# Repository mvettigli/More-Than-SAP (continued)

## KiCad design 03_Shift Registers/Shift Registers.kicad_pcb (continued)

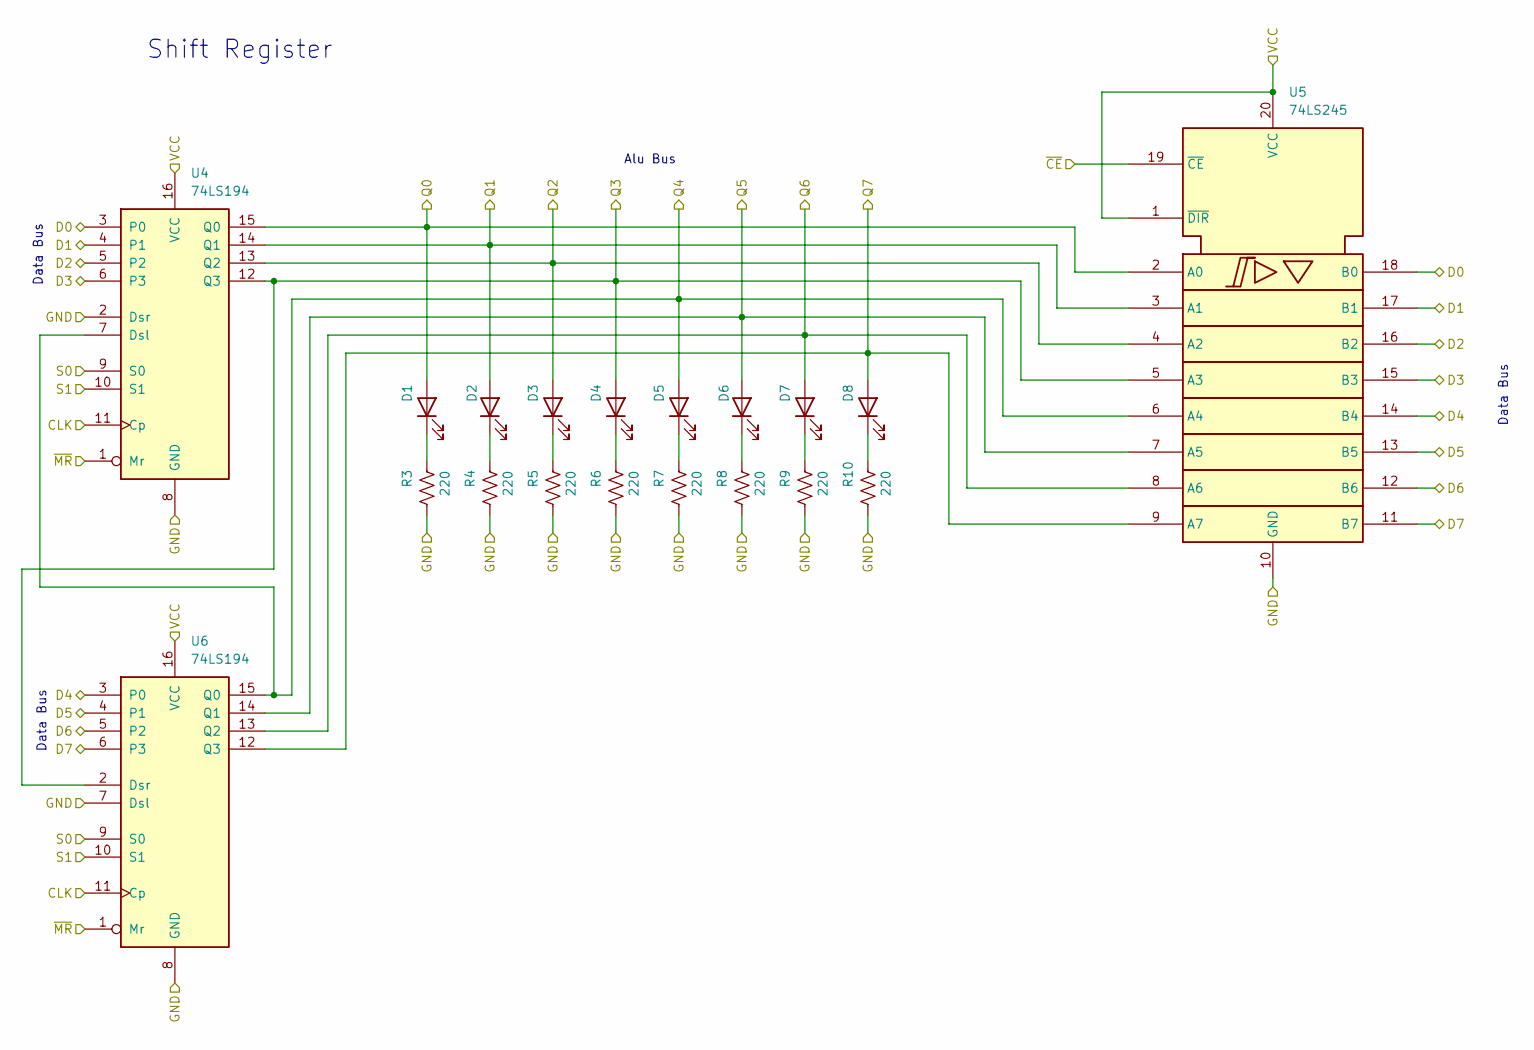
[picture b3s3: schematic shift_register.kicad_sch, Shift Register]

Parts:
D1, D2, D3, D4, D5, D6, D7, D8: RED; LED_D3.0mm
R3, R4, R5, R6, R7, R8, R9, R10: 220; R_Axial_DIN0207_L6.3mm_D2.5mm_P10.16mm_Horizontal
U4, U6: 74LS194; DIP-16_W7.62mm
U5: 74LS245; DIP-20_W7.62mm

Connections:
/Alu selector L-X/Q0: D1.2 (A), U4.15 (Q0), U5.2 (A0); also elsewhere on the board
/Alu selector L-X/Q1: D2.2 (A), U4.14 (Q1), U5.3 (A1); also elsewhere on the board
/Alu selector L-X/Q2: D3.2 (A), U4.13 (Q2), U5.4 (A2); also elsewhere on the board
/Alu selector L-X/Q3: D4.2 (A), U4.12 (Q3), U5.5 (A3), U6.2 (Dsr); also elsewhere on the board
/Alu selector L-X/Q4: D5.2 (A), U4.7 (Dsl), U5.6 (A4), U6.15 (Q0); also elsewhere on the board
/Alu selector L-X/Q5: D6.2 (A), U5.7 (A5), U6.14 (Q1); also elsewhere on the board
/Alu selector L-X/Q6: D7.2 (A), U5.8 (A6), U6.13 (Q2); also elsewhere on the board
/Alu selector L-X/Q7: D8.2 (A), U5.9 (A7), U6.12 (Q3); also elsewhere on the board
/Shift register L/S0: U4.9 (S0), U6.9 (S0); also elsewhere on the board
/Shift register L/S1: U4.10 (S1), U6.10 (S1); also elsewhere on the board
/Shift register L/~MR: U4.1 (Mr), U6.1 (Mr)
CLK: U4.11 (Cp), U6.11 (Cp); also elsewhere on the board
D0: U4.3 (P0), U5.18 (B0); also elsewhere on the board
D1: U4.4 (P1), U5.17 (B1); also elsewhere on the board
D2: U4.5 (P2), U5.16 (B2); also elsewhere on the board
D3: U4.6 (P3), U5.15 (B3); also elsewhere on the board
D4: U5.14 (B4), U6.3 (P0); also elsewhere on the board
D5: U5.13 (B5), U6.4 (P1); also elsewhere on the board
D6: U5.12 (B6), U6.5 (P2); also elsewhere on the board
D7: U5.11 (B7), U6.6 (P3); also elsewhere on the board
GND: R3.2, R4.2, R5.2, R6.2, R7.2, R8.2, R9.2, R10.2, U4.2 (Dsr), U4.8 (GND), U5.10 (GND), U6.7 (Dsl), U6.8 (GND); also elsewhere on the board
unnamed: D1.1 (K), R3.1
unnamed: D2.1 (K), R4.1
unnamed: D3.1 (K), R5.1
unnamed: D4.1 (K), R6.1
unnamed: D5.1 (K), R7.1
unnamed: D6.1 (K), R8.1
unnamed: D7.1 (K), R9.1
unnamed: D8.1 (K), R10.1
VCC: U4.16 (VCC), U5.1 (~DIR), U5.20 (VCC), U6.16 (VCC); also elsewhere on the board
~LRO: U5.19 (~CE); also elsewhere on the board

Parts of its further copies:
D9, D10, D11, D12, D13, D14, D15, D16: RED; LED_D3.0mm
R11, R12, R13, R14, R15, R16, R17, R18: 220; R_Axial_DIN0207_L6.3mm_D2.5mm_P10.16mm_Horizontal
U7, U9: 74LS194; DIP-16_W7.62mm
U8: 74LS245; DIP-20_W7.62mm

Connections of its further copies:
/Alu selector R-X/Q0: D9.2 (A), U7.15 (Q0), U8.2 (A0); also elsewhere on the board
/Alu selector R-X/Q1: D10.2 (A), U7.14 (Q1), U8.3 (A1); also elsewhere on the board
/Alu selector R-X/Q2: D11.2 (A), U7.13 (Q2), U8.4 (A2); also elsewhere on the board
/Alu selector R-X/Q3: D12.2 (A), U7.12 (Q3), U8.5 (A3), U9.2 (Dsr); also elsewhere on the board
/Alu selector R-X/Q4: D13.2 (A), U7.7 (Dsl), U8.6 (A4), U9.15 (Q0); also elsewhere on the board
/Alu selector R-X/Q5: D14.2 (A), U8.7 (A5), U9.14 (Q1); also elsewhere on the board
/Alu selector R-X/Q6: D15.2 (A), U8.8 (A6), U9.13 (Q2); also elsewhere on the board
/Alu selector R-X/Q7: D16.2 (A), U8.9 (A7), U9.12 (Q3); also elsewhere on the board
/Shift register R/S0: U7.9 (S0), U9.9 (S0); also elsewhere on the board
/Shift register R/S1: U7.10 (S1), U9.10 (S1); also elsewhere on the board
/Shift register R/~MR: U7.1 (Mr), U9.1 (Mr)
CLK: U7.11 (Cp), U9.11 (Cp); also elsewhere on the board
D0: U7.3 (P0), U8.18 (B0); also elsewhere on the board
D1: U7.4 (P1), U8.17 (B1); also elsewhere on the board
D2: U7.5 (P2), U8.16 (B2); also elsewhere on the board
D3: U7.6 (P3), U8.15 (B3); also elsewhere on the board
D4: U8.14 (B4), U9.3 (P0); also elsewhere on the board
D5: U8.13 (B5), U9.4 (P1); also elsewhere on the board
D6: U8.12 (B6), U9.5 (P2); also elsewhere on the board
D7: U8.11 (B7), U9.6 (P3); also elsewhere on the board
GND: R11.2, R12.2, R13.2, R14.2, R15.2, R16.2, R17.2, R18.2, U7.2 (Dsr), U7.8 (GND), U8.10 (GND), U9.7 (Dsl), U9.8 (GND); also elsewhere on the board
unnamed: D9.1 (K), R11.1
unnamed: D10.1 (K), R12.1
unnamed: D11.1 (K), R13.1
unnamed: D12.1 (K), R14.1
unnamed: D13.1 (K), R15.1
unnamed: D14.1 (K), R16.1
unnamed: D15.1 (K), R17.1
unnamed: D16.1 (K), R18.1
VCC: U7.16 (VCC), U8.1 (~DIR), U8.20 (VCC), U9.16 (VCC); also elsewhere on the board
~RRO: U8.19 (~CE); also elsewhere on the board

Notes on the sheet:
Data Bus
Shift Register
Alu Bus

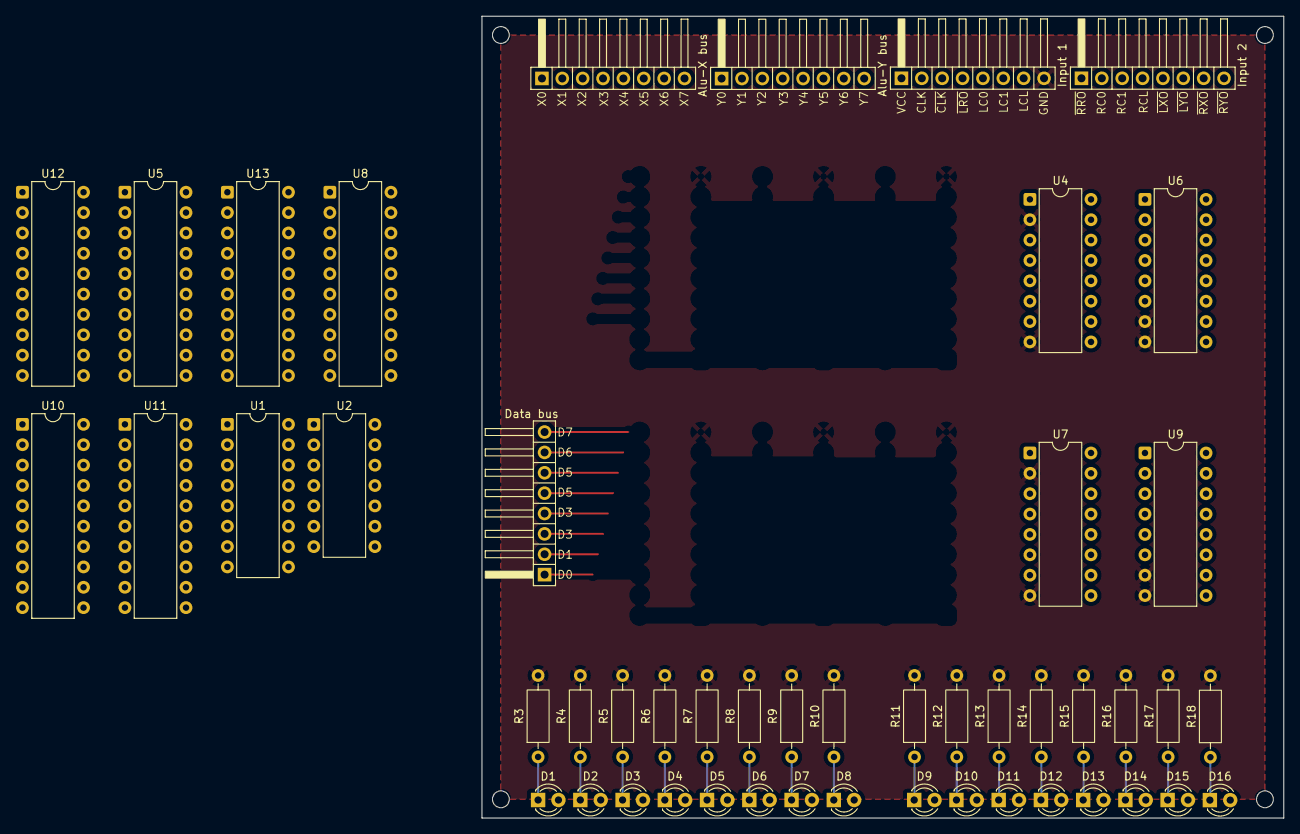
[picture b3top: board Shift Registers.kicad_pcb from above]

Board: 2 copper layers, 100.0 x 100.0 mm, 49 parts (0 on the bottom side), 81 nets.

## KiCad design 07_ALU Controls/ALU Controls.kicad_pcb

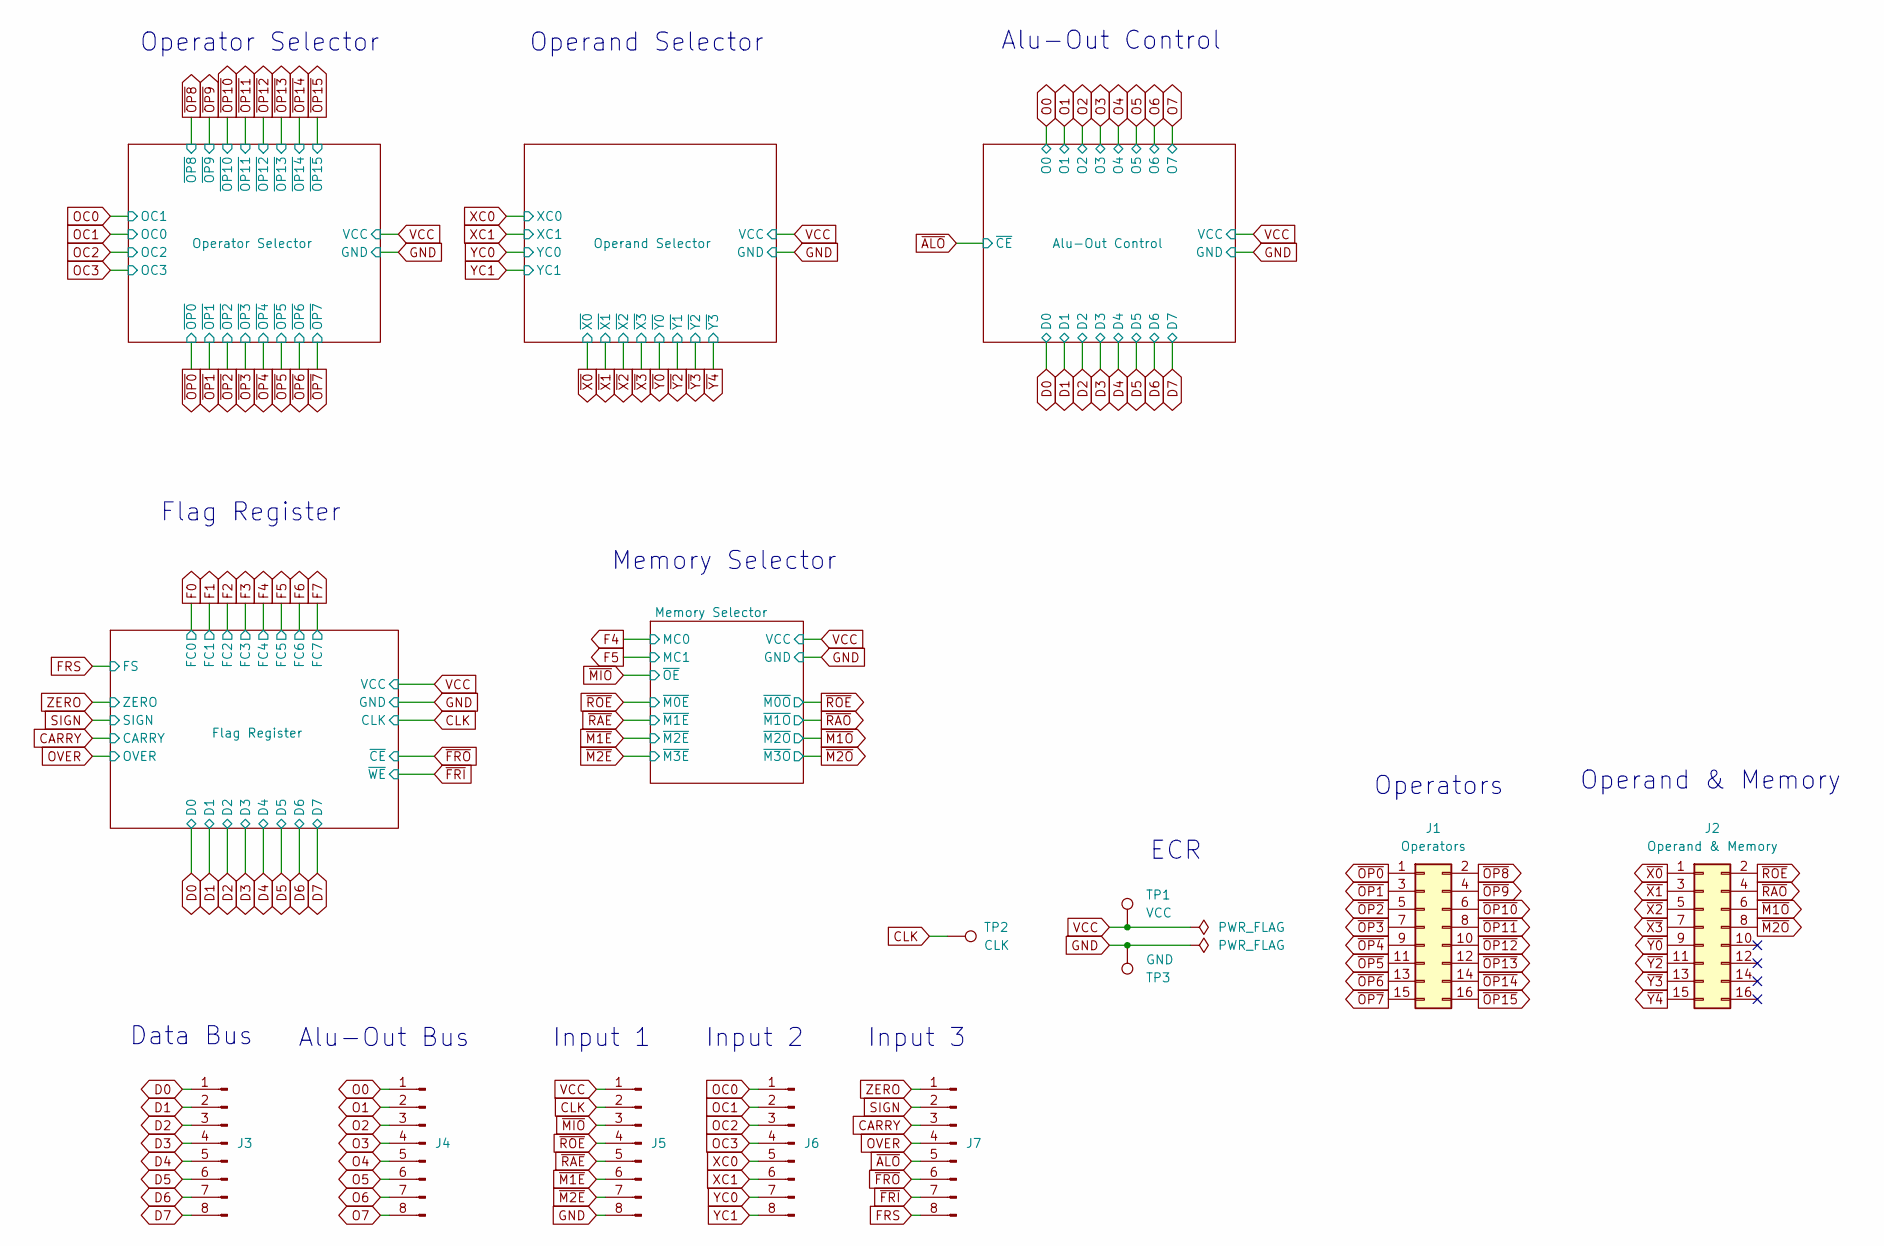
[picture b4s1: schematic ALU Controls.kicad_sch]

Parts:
J1: Operators; PinHeader_2x08_P2.54mm_Horizontal
J2: Operand & Memory; PinHeader_2x08_P2.54mm_Horizontal
J3: Data Bus; PinHeader_1x08_P2.54mm_Horizontal
J4: Alu-Out Bus; PinHeader_1x08_P2.54mm_Horizontal
J5: Input 1; PinHeader_1x08_P2.54mm_Horizontal
J6: Input 2; PinHeader_1x08_P2.54mm_Horizontal
J7: Input 3; PinHeader_1x08_P2.54mm_Horizontal
TP1: VCC; TestPoint_Loop_D3.50mm_Drill0.9mm_Beaded
TP2: CLK; TestPoint_Loop_D3.50mm_Drill0.9mm_Beaded
TP3: GND; TestPoint_Loop_D3.50mm_Drill0.9mm_Beaded

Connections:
CARRY: J7.3; also elsewhere on the board
CLK: J5.2, TP2.1; also elsewhere on the board
D0: J3.1; also elsewhere on the board
D1: J3.2; also elsewhere on the board
D2: J3.3; also elsewhere on the board
D3: J3.4; also elsewhere on the board
D4: J3.5; also elsewhere on the board
D5: J3.6; also elsewhere on the board
D6: J3.7; also elsewhere on the board
D7: J3.8; also elsewhere on the board
FRS: J7.8; also elsewhere on the board
GND: J5.8, TP3.1; also elsewhere on the board
O0: J4.1; also elsewhere on the board
O1: J4.2; also elsewhere on the board
O2: J4.3; also elsewhere on the board
O3: J4.4; also elsewhere on the board
O4: J4.5; also elsewhere on the board
O5: J4.6; also elsewhere on the board
O6: J4.7; also elsewhere on the board
O7: J4.8; also elsewhere on the board
OC0: J6.1; also elsewhere on the board
OC1: J6.2; also elsewhere on the board
OC2: J6.3; also elsewhere on the board
OC3: J6.4; also elsewhere on the board
OVER: J7.4; also elsewhere on the board
SIGN: J7.2; also elsewhere on the board
VCC: J5.1, TP1.1; also elsewhere on the board
XC0: J6.5; also elsewhere on the board
XC1: J6.6; also elsewhere on the board
YC0: J6.7; also elsewhere on the board
YC1: J6.8; also elsewhere on the board
ZERO: J7.1; also elsewhere on the board
~ALO: J7.5; also elsewhere on the board
~FRI: J7.7; also elsewhere on the board
~FRO: J7.6; also elsewhere on the board
~M1E: J5.6; also elsewhere on the board
~M1O: J2.6; also elsewhere on the board
~M2E: J5.7; also elsewhere on the board
~M2O: J2.8; also elsewhere on the board
~MIO: J5.3; also elsewhere on the board
~OP0: J1.1; also elsewhere on the board
~OP1: J1.3; also elsewhere on the board
~OP2: J1.5; also elsewhere on the board
~OP3: J1.7; also elsewhere on the board
~OP4: J1.9; also elsewhere on the board
~OP5: J1.11; also elsewhere on the board
~OP6: J1.13; also elsewhere on the board
~OP7: J1.15; also elsewhere on the board
~OP8: J1.2; also elsewhere on the board
~OP9: J1.4; also elsewhere on the board
~OP10: J1.6; also elsewhere on the board
~OP11: J1.8; also elsewhere on the board
~OP12: J1.10; also elsewhere on the board
~OP13: J1.12; also elsewhere on the board
~OP14: J1.14; also elsewhere on the board
~OP15: J1.16; also elsewhere on the board
~RAE: J5.5; also elsewhere on the board
~RAO: J2.4; also elsewhere on the board
~ROE: J2.2, J5.4; also elsewhere on the board
~X0: J2.1; also elsewhere on the board
~X1: J2.3; also elsewhere on the board
~X2: J2.5; also elsewhere on the board
~X3: J2.7; also elsewhere on the board
~Y0: J2.9; also elsewhere on the board
~Y2: J2.11; also elsewhere on the board
~Y3: J2.13; also elsewhere on the board
~Y4: J2.15; also elsewhere on the board

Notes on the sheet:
Flag Register
Memory Selector
Operand Selector
Operators
Operator Selector
Data Bus
ECR
Input 3
Alu-Out Bus
Operand & Memory
Input 2
Input 1
Alu-Out Control

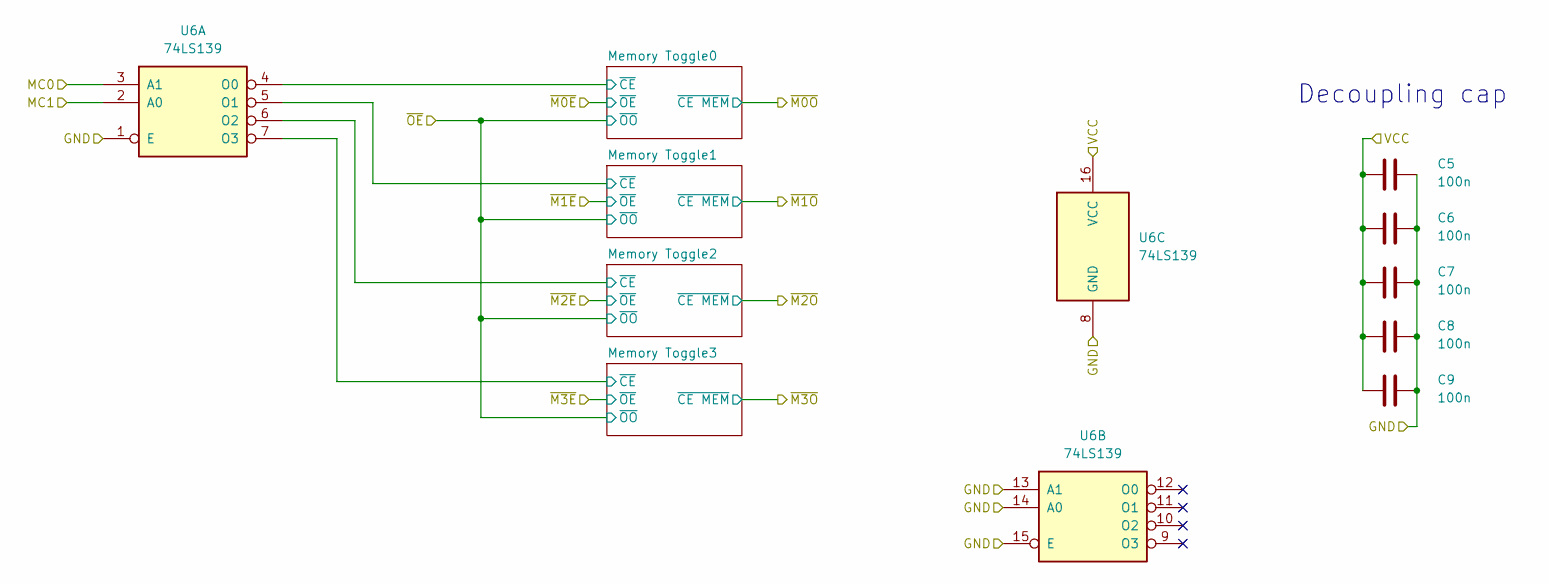
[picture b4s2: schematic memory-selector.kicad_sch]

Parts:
C5, C6, C7, C8, C9: 100n; C_Disc_D3.0mm_W1.6mm_P2.50mm
U6: 74LS139; DIP-16_W7.62mm

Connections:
/Memory Selector/Memory Toggle0/~CE: U6.4 (O0); also elsewhere on the board
/Memory Selector/Memory Toggle1/~CE: U6.5 (O1); also elsewhere on the board
/Memory Selector/Memory Toggle2/~CE: U6.6 (O2); also elsewhere on the board
/Memory Selector/Memory Toggle3/~CE: U6.7 (O3); also elsewhere on the board
F4: U6.3 (A1); also elsewhere on the board
F5: U6.2 (A0); also elsewhere on the board
GND: C5.2, C6.2, C7.2, C8.2, C9.2, U6.1 (E), U6.8 (GND), U6.13 (A1), U6.14 (A0), U6.15 (E); also elsewhere on the board
VCC: C5.1, C6.1, C7.1, C8.1, C9.1, U6.16 (VCC); also elsewhere on the board

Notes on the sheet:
Decoupling cap

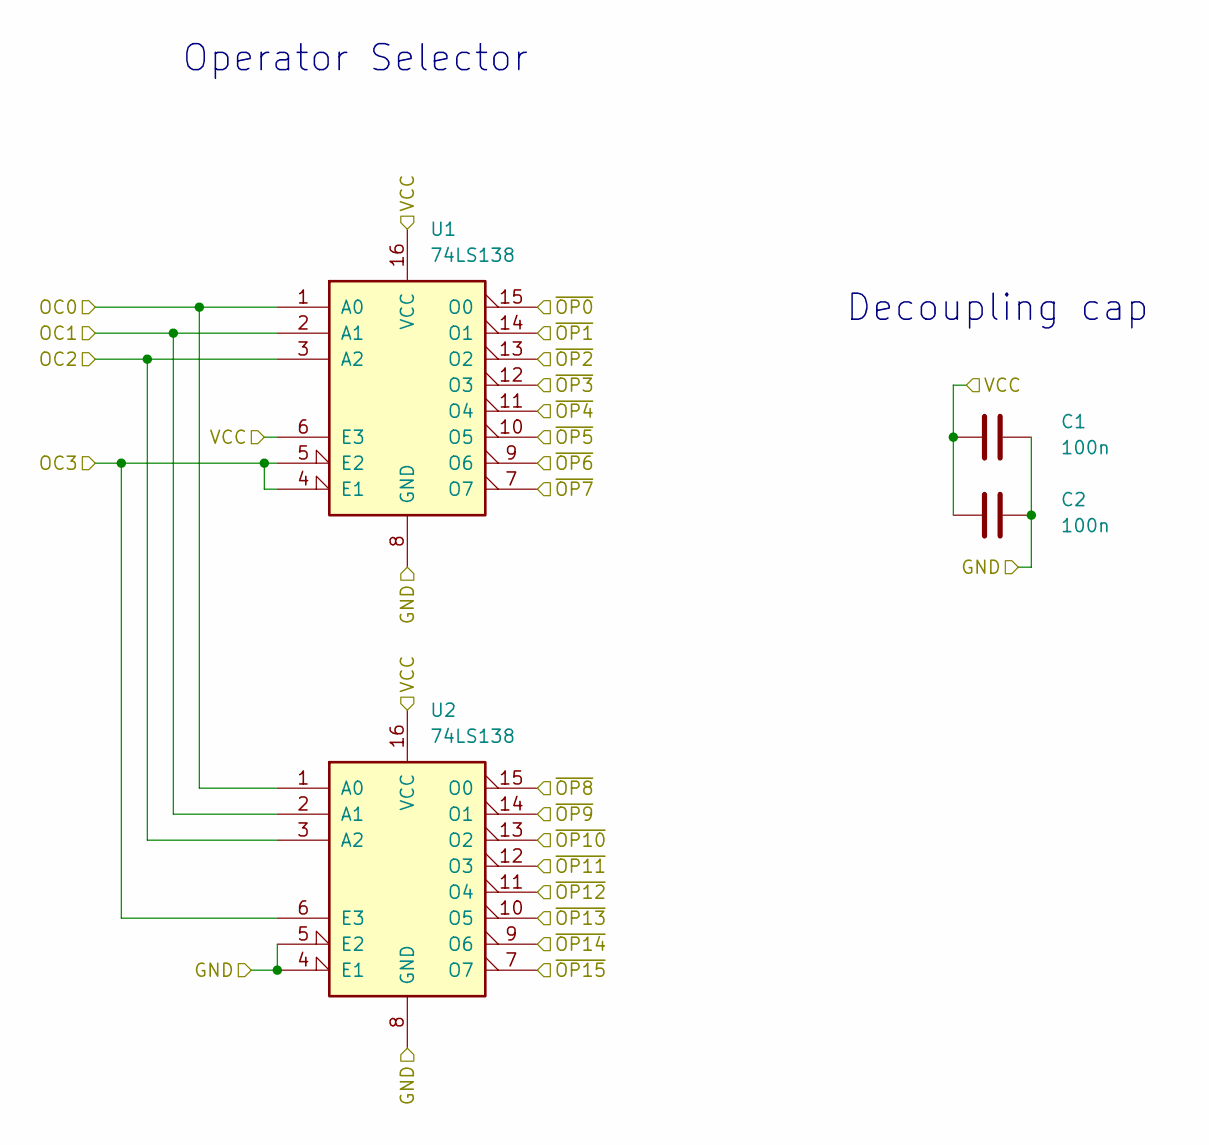
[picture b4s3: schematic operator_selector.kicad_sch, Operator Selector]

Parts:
C1, C2: 100n; C_Disc_D3.0mm_W1.6mm_P2.50mm
U1, U2: 74LS138; DIP-16_W10.16mm

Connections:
GND: C1.2, C2.2, U1.8 (GND), U2.4 (E1), U2.5 (E2), U2.8 (GND); also elsewhere on the board
OC0: U1.2 (A1), U2.2 (A1); also elsewhere on the board
OC1: U1.1 (A0), U2.1 (A0); also elsewhere on the board
OC2: U1.3 (A2), U2.3 (A2); also elsewhere on the board
OC3: U1.4 (E1), U1.5 (E2), U2.6 (E3); also elsewhere on the board
VCC: C1.1, C2.1, U1.6 (E3), U1.16 (VCC), U2.16 (VCC); also elsewhere on the board
~OP0: U1.15 (O0); also elsewhere on the board
~OP1: U1.14 (O1); also elsewhere on the board
~OP2: U1.13 (O2); also elsewhere on the board
~OP3: U1.12 (O3); also elsewhere on the board
~OP4: U1.11 (O4); also elsewhere on the board
~OP5: U1.10 (O5); also elsewhere on the board
~OP6: U1.9 (O6); also elsewhere on the board
~OP7: U1.7 (O7); also elsewhere on the board
~OP8: U2.15 (O0); also elsewhere on the board
~OP9: U2.14 (O1); also elsewhere on the board
~OP10: U2.13 (O2); also elsewhere on the board
~OP11: U2.12 (O3); also elsewhere on the board
~OP12: U2.11 (O4); also elsewhere on the board
~OP13: U2.10 (O5); also elsewhere on the board
~OP14: U2.9 (O6); also elsewhere on the board
~OP15: U2.7 (O7); also elsewhere on the board

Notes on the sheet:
Operator Selector
Decoupling cap

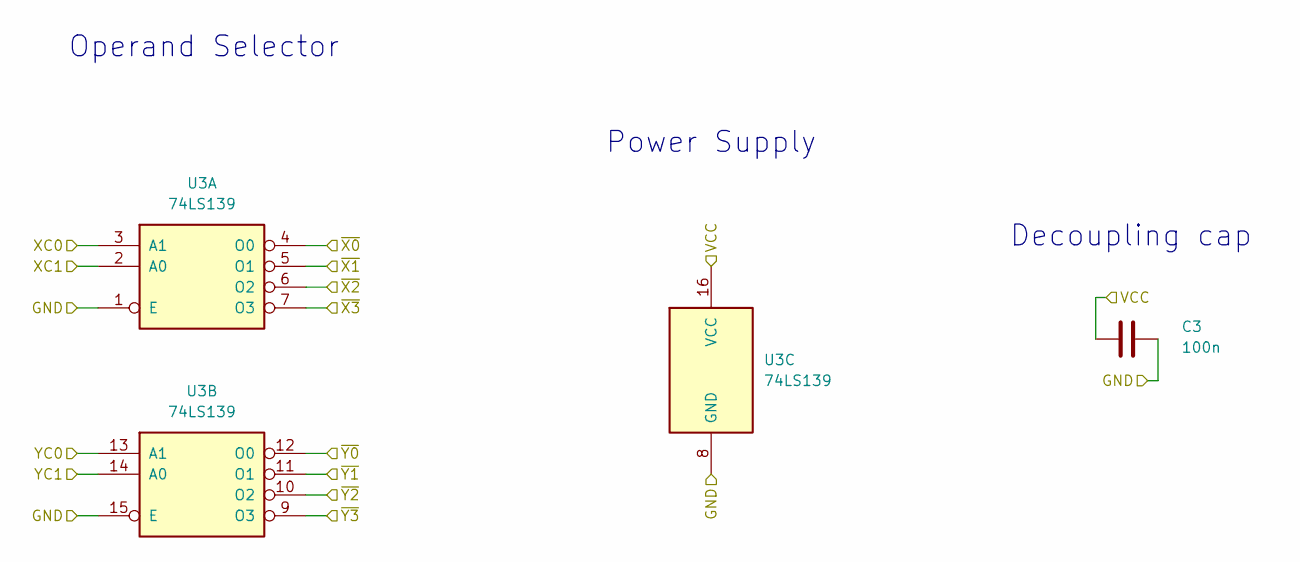
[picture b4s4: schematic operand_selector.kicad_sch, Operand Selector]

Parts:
C3: 100n; C_Disc_D3.0mm_W1.6mm_P2.50mm
U3: 74LS139; DIP-16_W10.16mm

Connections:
GND: C3.2, U3.1 (E), U3.8 (GND), U3.15 (E); also elsewhere on the board
VCC: C3.1, U3.16 (VCC); also elsewhere on the board
XC0: U3.3 (A1); also elsewhere on the board
XC1: U3.2 (A0); also elsewhere on the board
YC0: U3.13 (A1); also elsewhere on the board
YC1: U3.14 (A0); also elsewhere on the board
~X0: U3.4 (O0); also elsewhere on the board
~X1: U3.5 (O1); also elsewhere on the board
~X2: U3.6 (O2); also elsewhere on the board
~X3: U3.7 (O3); also elsewhere on the board
~Y0: U3.12 (O0); also elsewhere on the board
~Y2: U3.11 (O1); also elsewhere on the board
~Y3: U3.10 (O2); also elsewhere on the board
~Y4: U3.9 (O3); also elsewhere on the board

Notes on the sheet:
Operand Selector
Decoupling cap
Power Supply

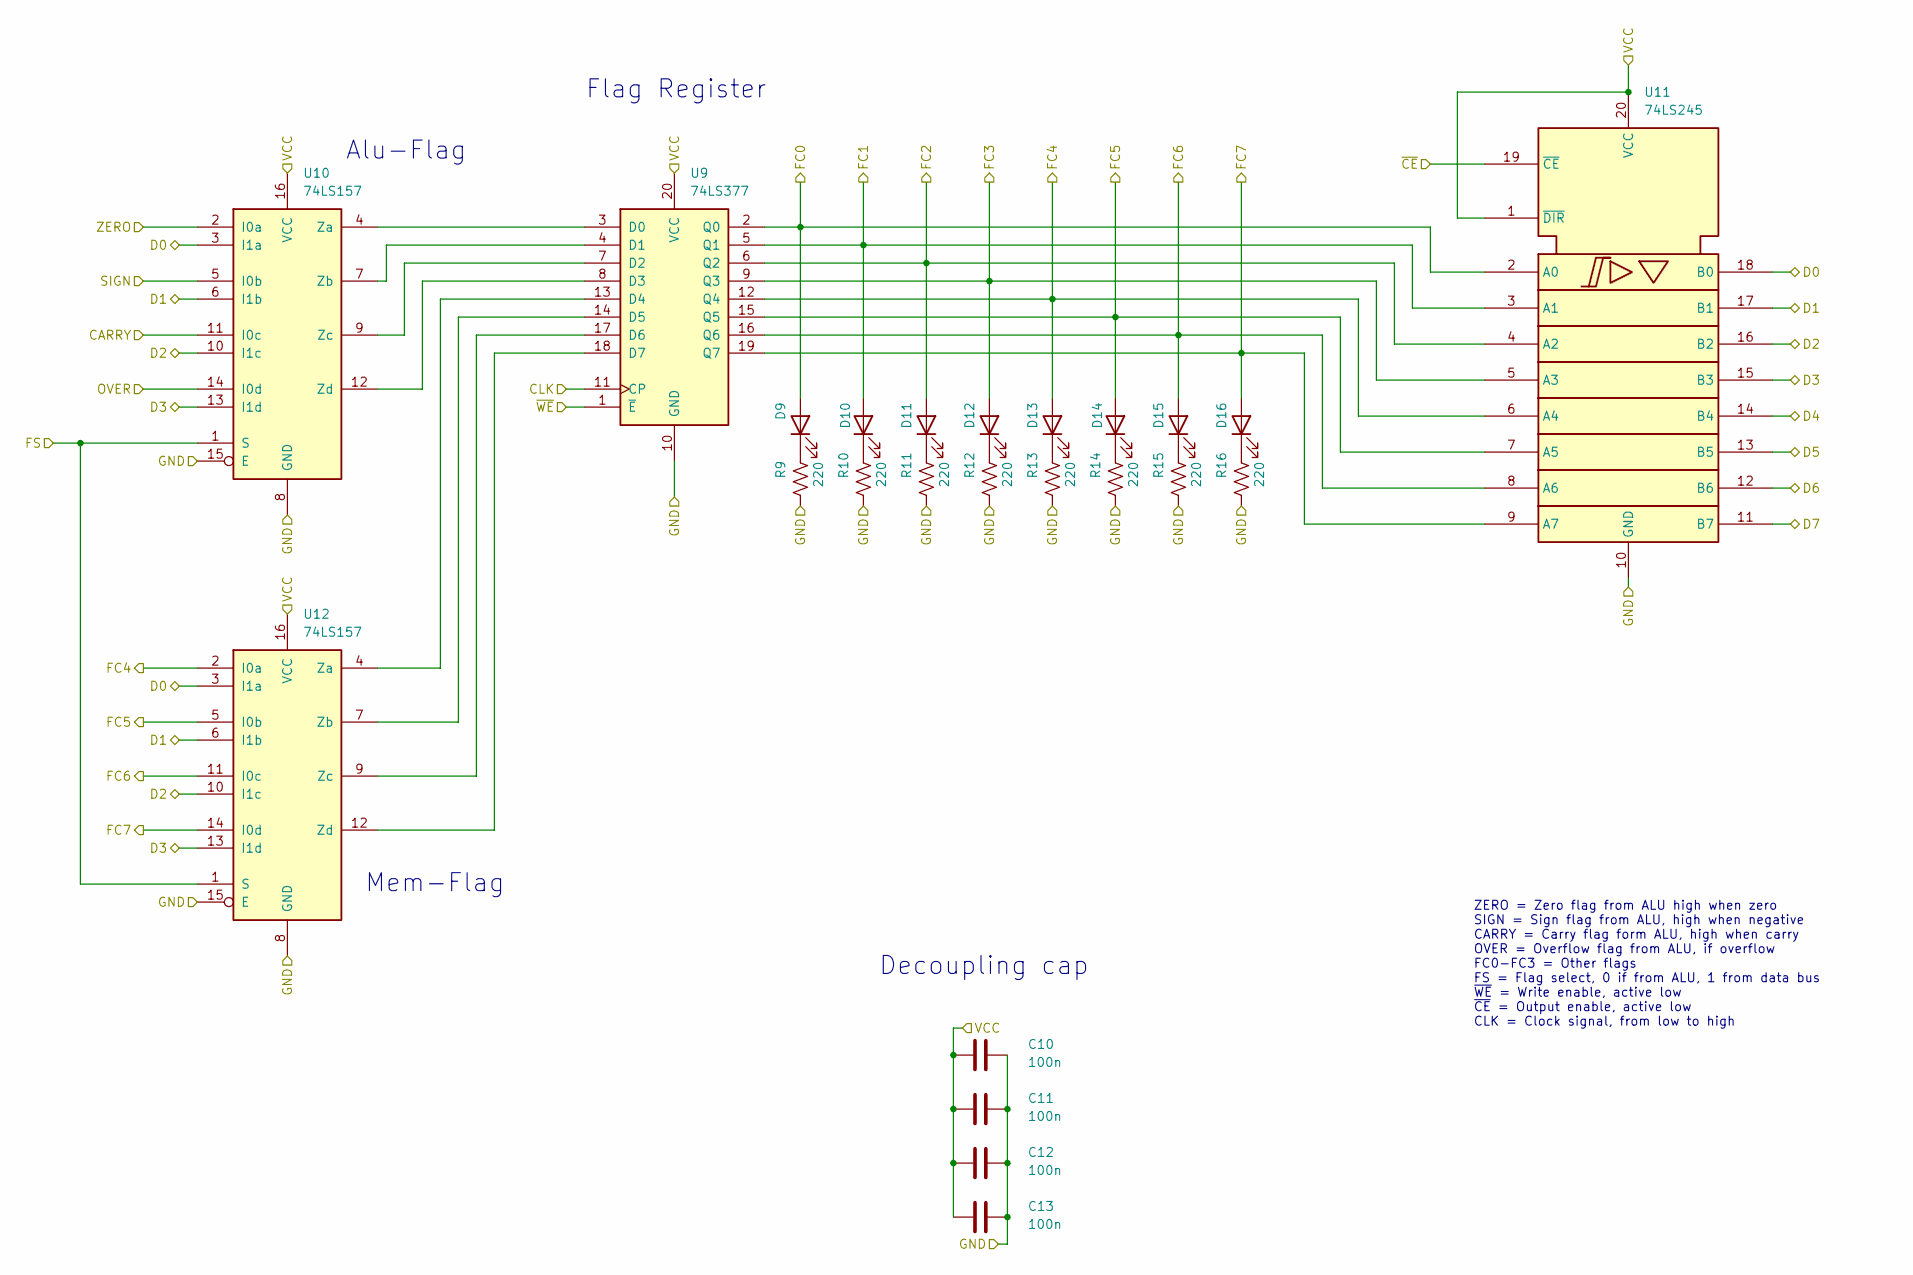
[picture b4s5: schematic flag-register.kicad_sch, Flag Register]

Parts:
C10, C11, C12, C13: 100n; C_Disc_D3.0mm_W1.6mm_P2.50mm
D9, D10, D11, D12, D13, D14, D15, D16: ORA; LED_D3.0mm
R9, R10, R11, R12, R13, R14, R15, R16: 220; R_Axial_DIN0207_L6.3mm_D2.5mm_P10.16mm_Horizontal
U9: 74LS377; DIP-20_W7.62mm
U10, U12: 74LS157; DIP-16_W7.62mm
U11: 74LS245; DIP-20_W7.62mm

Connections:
CARRY: U10.11 (I0c); also elsewhere on the board
CLK: U9.11 (CP); also elsewhere on the board
D0: U10.3 (I1a), U11.18 (B0), U12.3 (I1a); also elsewhere on the board
D1: U10.6 (I1b), U11.17 (B1), U12.6 (I1b); also elsewhere on the board
D2: U10.10 (I1c), U11.16 (B2), U12.10 (I1c); also elsewhere on the board
D3: U10.13 (I1d), U11.15 (B3), U12.13 (I1d); also elsewhere on the board
D4: U11.14 (B4); also elsewhere on the board
D5: U11.13 (B5); also elsewhere on the board
D6: U11.12 (B6); also elsewhere on the board
D7: U11.11 (B7); also elsewhere on the board
F0: D9.2 (A), U9.2 (Q0), U11.2 (A0)
F1: D10.2 (A), U9.5 (Q1), U11.3 (A1)
F2: D11.2 (A), U9.6 (Q2), U11.4 (A2)
F3: D12.2 (A), U9.9 (Q3), U11.5 (A3)
F4: D13.2 (A), U9.12 (Q4), U11.6 (A4), U12.2 (I0a); also elsewhere on the board
F5: D14.2 (A), U9.15 (Q5), U11.7 (A5), U12.5 (I0b); also elsewhere on the board
F6: D15.2 (A), U9.16 (Q6), U11.8 (A6), U12.11 (I0c)
F7: D16.2 (A), U9.19 (Q7), U11.9 (A7), U12.14 (I0d)
FRS: U10.1 (S), U12.1 (S); also elsewhere on the board
GND: C10.2, C11.2, C12.2, C13.2, R9.2, R10.2, R11.2, R12.2, R13.2, R14.2, R15.2, R16.2, U9.10 (GND), U10.8 (GND), U10.15 (E), U11.10 (GND), U12.8 (GND), U12.15 (E); also elsewhere on the board
unnamed: D9.1 (K), R9.1
unnamed: D10.1 (K), R10.1
unnamed: D11.1 (K), R11.1
unnamed: D12.1 (K), R12.1
unnamed: D13.1 (K), R13.1
unnamed: D14.1 (K), R14.1
unnamed: D15.1 (K), R15.1
unnamed: D16.1 (K), R16.1
unnamed: U9.3 (D0), U10.4 (Za)
unnamed: U9.4 (D1), U10.7 (Zb)
unnamed: U9.7 (D2), U10.9 (Zc)
unnamed: U9.8 (D3), U10.12 (Zd)
unnamed: U9.13 (D4), U12.4 (Za)
unnamed: U9.14 (D5), U12.7 (Zb)
unnamed: U9.17 (D6), U12.9 (Zc)
unnamed: U9.18 (D7), U12.12 (Zd)
OVER: U10.14 (I0d); also elsewhere on the board
SIGN: U10.5 (I0b); also elsewhere on the board
VCC: C10.1, C11.1, C12.1, C13.1, U9.20 (VCC), U10.16 (VCC), U11.1 (~DIR), U11.20 (VCC), U12.16 (VCC); also elsewhere on the board
ZERO: U10.2 (I0a); also elsewhere on the board
~FRI: U9.1 (~E); also elsewhere on the board
~FRO: U11.19 (~CE); also elsewhere on the board

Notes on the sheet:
Flag Register
Alu-Flag
Mem-Flag
Decoupling cap
ZERO = Zero flag from ALU high when zero SIGN = Sign flag from ALU, high when negative CARRY = Carry flag form ALU, high when carry OVER = Overflow flag from ALU, if overflow FC0-FC3 = Other flags FS = Flag select, 0 if from ALU, 1 from data bus ~{WE} = Write enable, active low ~{CE} = Output enabl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

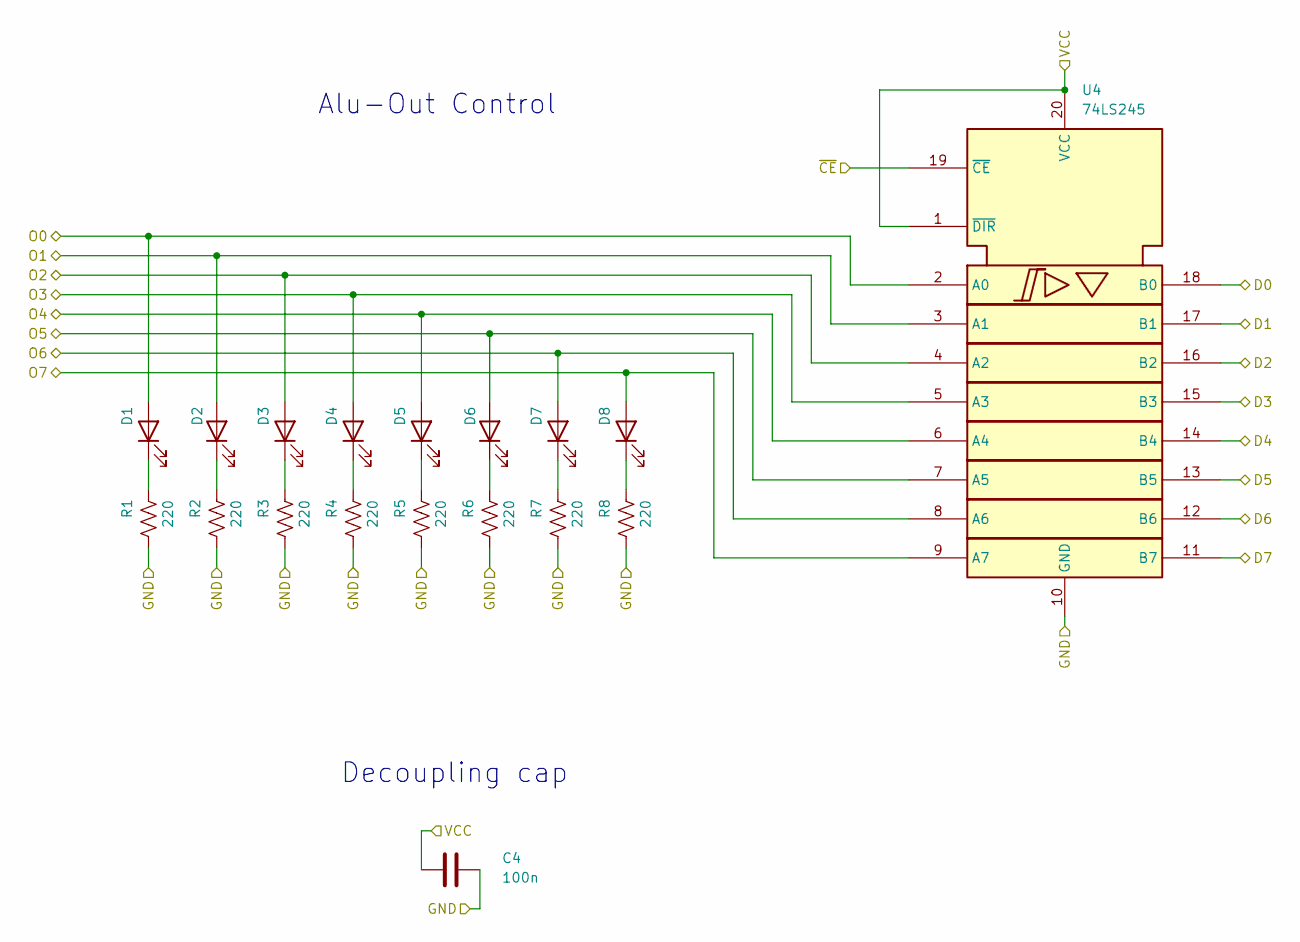
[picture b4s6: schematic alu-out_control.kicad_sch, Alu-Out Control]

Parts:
C4: 100n; C_Disc_D3.0mm_W1.6mm_P2.50mm
D1, D2, D3, D4, D5, D6, D7, D8: RED; LED_D3.0mm
R1, R2, R3, R4, R5, R6, R7, R8: 220; R_Axial_DIN0207_L6.3mm_D2.5mm_P10.16mm_Horizontal
U4: 74LS245; DIP-20_W7.62mm

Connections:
D0: U4.18 (B0); also elsewhere on the board
D1: U4.17 (B1); also elsewhere on the board
D2: U4.16 (B2); also elsewhere on the board
D3: U4.15 (B3); also elsewhere on the board
D4: U4.14 (B4); also elsewhere on the board
D5: U4.13 (B5); also elsewhere on the board
D6: U4.12 (B6); also elsewhere on the board
D7: U4.11 (B7); also elsewhere on the board
GND: C4.2, R1.2, R2.2, R3.2, R4.2, R5.2, R6.2, R7.2, R8.2, U4.10 (GND); also elsewhere on the board
unnamed: D1.1 (K), R1.1
unnamed: D2.1 (K), R2.1
unnamed: D3.1 (K), R3.1
unnamed: D4.1 (K), R4.1
unnamed: D5.1 (K), R5.1
unnamed: D6.1 (K), R6.1
unnamed: D7.1 (K), R7.1
unnamed: D8.1 (K), R8.1
O0: D1.2 (A), U4.2 (A0); also elsewhere on the board
O1: D2.2 (A), U4.3 (A1); also elsewhere on the board
O2: D3.2 (A), U4.4 (A2); also elsewhere on the board
O3: D4.2 (A), U4.5 (A3); also elsewhere on the board
O4: D5.2 (A), U4.6 (A4); also elsewhere on the board
O5: D6.2 (A), U4.7 (A5); also elsewhere on the board
O6: D7.2 (A), U4.8 (A6); also elsewhere on the board
O7: D8.2 (A), U4.9 (A7); also elsewhere on the board
VCC: C4.1, U4.1 (~DIR), U4.20 (VCC); also elsewhere on the board
~ALO: U4.19 (~CE); also elsewhere on the board

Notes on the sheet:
Alu-Out Control
Decoupling cap

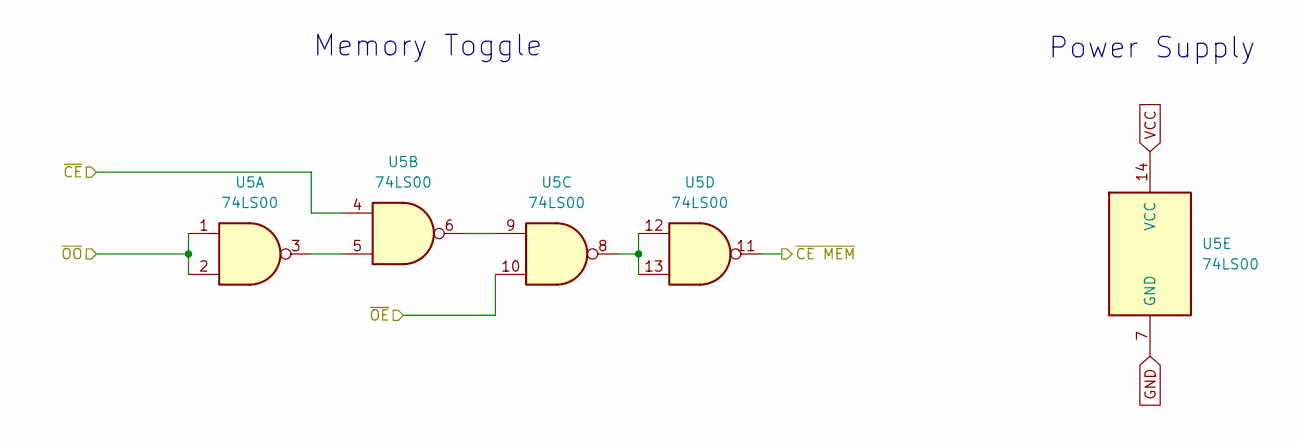
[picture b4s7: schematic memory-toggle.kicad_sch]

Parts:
U5: 74LS00; DIP-14_W7.62mm

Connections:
/Memory Selector/Memory Toggle0/~CE: U5.4; also elsewhere on the board
GND: U5.7 (GND); also elsewhere on the board
unnamed: U5.3, U5.5
unnamed: U5.6, U5.9
unnamed: U5.8, U5.12, U5.13
VCC: U5.14 (VCC); also elsewhere on the board
~MIO: U5.1, U5.2; also elsewhere on the board
~ROE: U5.10, U5.11; also elsewhere on the board

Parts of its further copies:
U7, U8, U13: 74LS00; DIP-14_W7.62mm

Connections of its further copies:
/Memory Selector/Memory Toggle1/~CE: U7.4; also elsewhere on the board
/Memory Selector/Memory Toggle2/~CE: U8.4; also elsewhere on the board
/Memory Selector/Memory Toggle3/~CE: U13.4; also elsewhere on the board
GND: U7.7 (GND), U8.7 (GND), U13.7 (GND); also elsewhere on the board
unnamed: U7.3, U7.5
unnamed: U7.6, U7.9
unnamed: U7.8, U7.12, U7.13
unnamed: U8.3, U8.5
unnamed: U8.6, U8.9
unnamed: U8.8, U8.12, U8.13
unnamed: U13.3, U13.5
unnamed: U13.6, U13.9
unnamed: U13.8, U13.12, U13.13
VCC: U7.14 (VCC), U8.14 (VCC), U13.14 (VCC); also elsewhere on the board
~M1E: U8.10; also elsewhere on the board
~M1O: U8.11; also elsewhere on the board
~M2E: U13.10; also elsewhere on the board
~M2O: U13.11; also elsewhere on the board
~MIO: U7.1, U7.2, U8.1, U8.2, U13.1, U13.2; also elsewhere on the board
~RAE: U7.10; also elsewhere on the board
~RAO: U7.11; also elsewhere on the board

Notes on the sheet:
Memory Toggle
Power Supply
